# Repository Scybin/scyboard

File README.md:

# scyboard

## 📚 Table of Contents

- [⚠️ Disclaimer](#disclaimer)
- [⌨️ Welcome](#welcome)
- [⚙️ Features](#features)
- [📊 Project Status](#project-status)
- [📦 Parts List](#parts-list)
- [🛠️ Build Guide](#build-guide)
- [💾 Firmware](#firmware)
- [🙏 Thanks](#thanks)
- [📄 License](#license)

## ⚠️ Disclaimer

This project has reached the fully working prototype stage. All core features have been tested and function as intended. However, as with any DIY hardware project, you should carefully review all files before manufacturing or assembly. The author(s) cannot guarantee flawless operation in every environment or configuration.

The author(s) take no responsibility for any damage, issues, or legal trouble that might result from using this project (see the license). Be sure to follow local laws regarding radio frequencies and DIY electronics.

## ⌨️ Welcome

Scyboard is a custom, open-source mechanical keyboard designed for ergonomic comfort and wireless functionality. Inspired by the Sweep and Corne keyboards, scyboard builds on these layouts and design principles. Every aspect was created using open-source tools, making it easy to modify, build, and share.

## ⚙️ Features

- Compact layout optimized for ergonomics
- ZMK firmware support
- USB-C connectivity & battery charging
- Bluetooth compatible
- Customizable keymaps, layers, and macros
- Layout is declared using Ergogen
- KiCad traces auto-routed using Freerouting
- Open source

## 📊 Project Status

The prototype has been built successfully. All aspects of the keyboard and firmware behave as expected.

## 📦 Parts List

*I am not sponsored or affiliated with the vendors linked below. This is where I prefer to purchase my products.*

| Part                     | Quantity | Description                          | Purchase Link                                                                                                         | Datasheet                                                                                                                                                         |
|--------------------------|----------|--------------------------------------|-----------------------------------------------------------------------------------------------------------------------|-------------------------------------------------------------------------------------------------------------------------------------------------------------------|
| Microcontroller          |    2     | nice!nano v2.0                       | [Nice Keyboarrds nice!nano v2.0](https://typeractive.xyz/products/no-solder-spring-headers?variant=47196312502503)    | [Nordic nRF52840](https://nicekeyboards.com/nice-nano)                                                                                                            | 
| Pin Headers              |    4     | Controller socketing system          | [MAC8 spring-loaded pin headers](https://typeractive.xyz/products/no-solder-spring-headers?variant=47196312502503)    | [MAC8 spring-loaded pin headers specifications](https://www.mac8sdk.co.jp/uploads/entry_meta/file_value/1117/mac8_2018a_jp-xb2.pdf)                               |
| Reset Button             |    2     | Panasonic miniature momentary button | [Panasonic Reset Button](https://typeractive.xyz/products/reset-button)                                               | [EVQPUC02K](https://cdn.shopify.com/s/files/1/0618/5674/3655/files/PANASONIC-EVQPUC02K.pdf)                                                                       |
| Power Switch             |    2     | Alps miniature SPDT switch           | [ALPS Powr Switch](https://typeractive.xyz/products/power-switch)                                                     | [SSSS811101](https://cdn.shopify.com/s/files/1/0618/5674/3655/files/ALPS-SSSS811101.pdf)                                                                          |
| Battery Jack             |    2     | JST PH 2.0mm                         | [JST Battery Jack](https://typeractive.xyz/products/battery-jack)                                                     | [JST_PH_S2B-PH-K_1x02_P2.00mm_Horizontal](http://www.jst-mfg.com/product/pdf/eng/ePH.pdf)                                                                         |
| Battery                  |    2     | 3.7V LiPo 110mAh (w/ JST adapter)    | [Liter Bihuade Lithium Battery](https://typeractive.xyz/products/lithium-battery-110mah)                              | [301230](https://www.ufinebattery.com/images/upload/ufx0509-08-3-7v-75mah-lithium-ion-battery-product-datasheet.pdf)                                              |
| Diode                    |    44    | SMD Diode                            | [Semtech SMD Diodes](https://typeractive.xyz/products/smd-diodes)                                                     | [SOD-123](https://www.onsemi.com/download/data-sheet/pdf/mmsd301t1-d.pdf)      									                                                                 |
| Hotswap Socket           |    44    | Kailh Choc PCB Socket                | [Kailh Hotswap Sockets](https://typeractive.xyz/products/hotswap-sockets)                                             | [1350Connector](https://www.kailhswitch.com/Content/upload/pdf/202115927/CPG135001S30-data-sheet.pdf?rnd=943)                                                     |
| Choc V1/V2 Switch        |    44    | Kailh Choc                           | [Lowprokb Ambients Silent Choc Switches](https://lowprokb.ca/products/ambients-silent-choc-switches)                  |                                                                                                                                                                   |
| Choc Keycap              |    44    | 40 x 1u, 4 x 1.5u                    | [FK MBK Choc Keycaps](https://typeractive.xyz/products/mbk-keycaps)                                                   |                                                                                                                                                                   |
| Nut  (optional)          |    12    | Inserts for bottom case              | [uxcell Knurled Insert Nuts](https://www.amazon.com/dp/B07LBQFNQD?th=1)                                               |                                                                                                                                                                   |
| M2X3 Screw  (optional)   |    24    | Screws for bottom case               | [CO-RODE Screw Kit](https://www.amazon.com/gp/product/B01FTI8TM8/)                                                    |                                                                                                                                                                   |
| M2X4 Screw  (optional)   |    12    | Screws for bottom case               | [CO-RODE Screw Kit](https://www.amazon.com/gp/product/B01FTI8TM8/)                                                    |                                                                                                                                                                   |
| M2X6 Standoff (optional) |    10    | Standoffs for plate                  | [uxcell M2x6 Standoffs](https://a.co/d/fXHgMmH)                                                                       |                                                                                                                                                                   |
| Bottom Case (optional)   |    2     | 3D printed bottom case               | [Case STL Found Here](https://github.com/Scybin/scyboard/tree/master/3d)                                              |                                                                                                                                                                   |
| Plate (optional)         |    2     | 3D printed plate                     | [Plate STL Found Here](https://github.com/Scybin/scyboard/tree/master/3d)                                             |                                                                                                                                                                   | 
| Screw Spacers (optional) |    12    | 3D printed spacers                   | [Screw Spacer STL Found Here](https://github.com/Scybin/scyboard/tree/master/3d)                                      |                                                                                                                                                                   |

## 🛠️ Build Guide

For assembling the keyboard hardware, I recommend following the guide for the Corne keyboard, as the assembly process is similar. You can find the guide here: [corne-cherry v2 buildguide](https://github.com/foostan/crkbd/blob/main/docs/corne-cherry/v2/buildguide_en.md)

In addition, here are some specific notes for the scyboard:
- There will be slight differences in the assembly process due to the different components used, but the overall steps will be similar.
- Place the nice!nano V2 microcontroller face down (flat side facing up).
- Solder the MCU jumper pads on the *same* (top) side of the PCB where the MCU wis mounted.
- Solder the JST battery connector jumpper pads on the *opposite* (back) side of the PCB where the MCU is mounted.

You can use the 3D printed bottom case without a plate. This requires M2x4 screws on the top, M2X3 screws on the bottom, knurled insert nuts, and 3D printed screw spacers. To mount the PCB directly to the case, use the 3D printed screw spacers between the screw and PCB. 

If you want to add a plate to the build, you can replace the nuts and spacers by using M2x6 standoffs. I included files for a plate if you decide to go this route. You will need one insert nut and spacer for the hole next to the JST connector since the plate does not cover this area.

## 💾 Firmware

A ZMK module for this keyboard is available at:  
[zmk-keyboard-scyboard](https://github.com/Scybin/zmk-keyboard-scyboard)

To get started, add the module to your west.yaml file and follow the flashing instructions in the ZMK docs.

## 🙏 Thanks

- **[Ergogen](https://docs.ergogen.xyz/):** For keyboard PCB generation and configuration.
- **[Ceoloide](https://github.com/ceoloide/ergogen-footprints):** For providing footprints. An additional thanks for code inspiration.
- **[ZMK Firmware](https://zmk.dev/):** For providing the open-source keyboard architecture support.
- **[KiCad](https://www.kicad.org/):** For PCB viewing and editing.
- **[Freerouting](https://www.freerouting.app/):** For PCB auto-routing in KiCad.
- **[typeractive](https://typeractive.xyz/):** For design and parts inspiration.
- **[Sweep by David Philip Barr](https://github.com/davidphilipbarr/Sweep):** For key matrix and column stagger inspiration.
- **[Corne by foostan](https://github.com/foostan/crkbd):** For thumb cluster inspiration.
- **[FlatFootFox](https://flatfootfox.com/ergogen-introduction/):** For an Ergogen tutorial.
- **[nickcoutsos](https://nickcoutsos.github.io/keymap-editor/):** For the ZMK Keymap Editor browser app.
- **[joe-scotto](https://github.com/Scybin/scottokeebs/tree/dab518b84248842a73bc8f1feb84828ada38bbac/Extras/ScottoKicad):** For a 3d model library
- Open Source Community: For sharing knowledge, scripts, and inspiration.

## 📄 License

This project is licensed under the MIT License. See the [LICENSE](LICENSE) file for details.

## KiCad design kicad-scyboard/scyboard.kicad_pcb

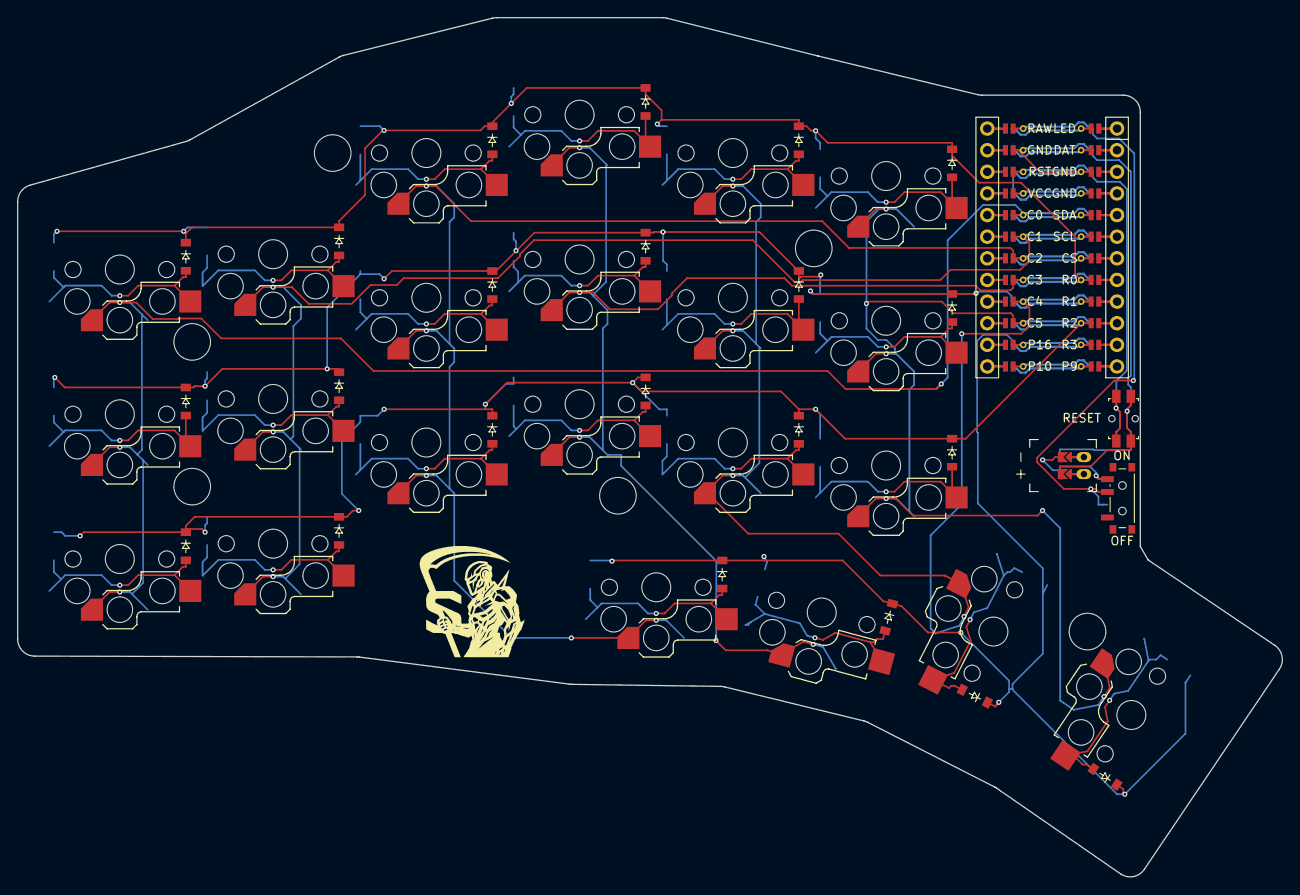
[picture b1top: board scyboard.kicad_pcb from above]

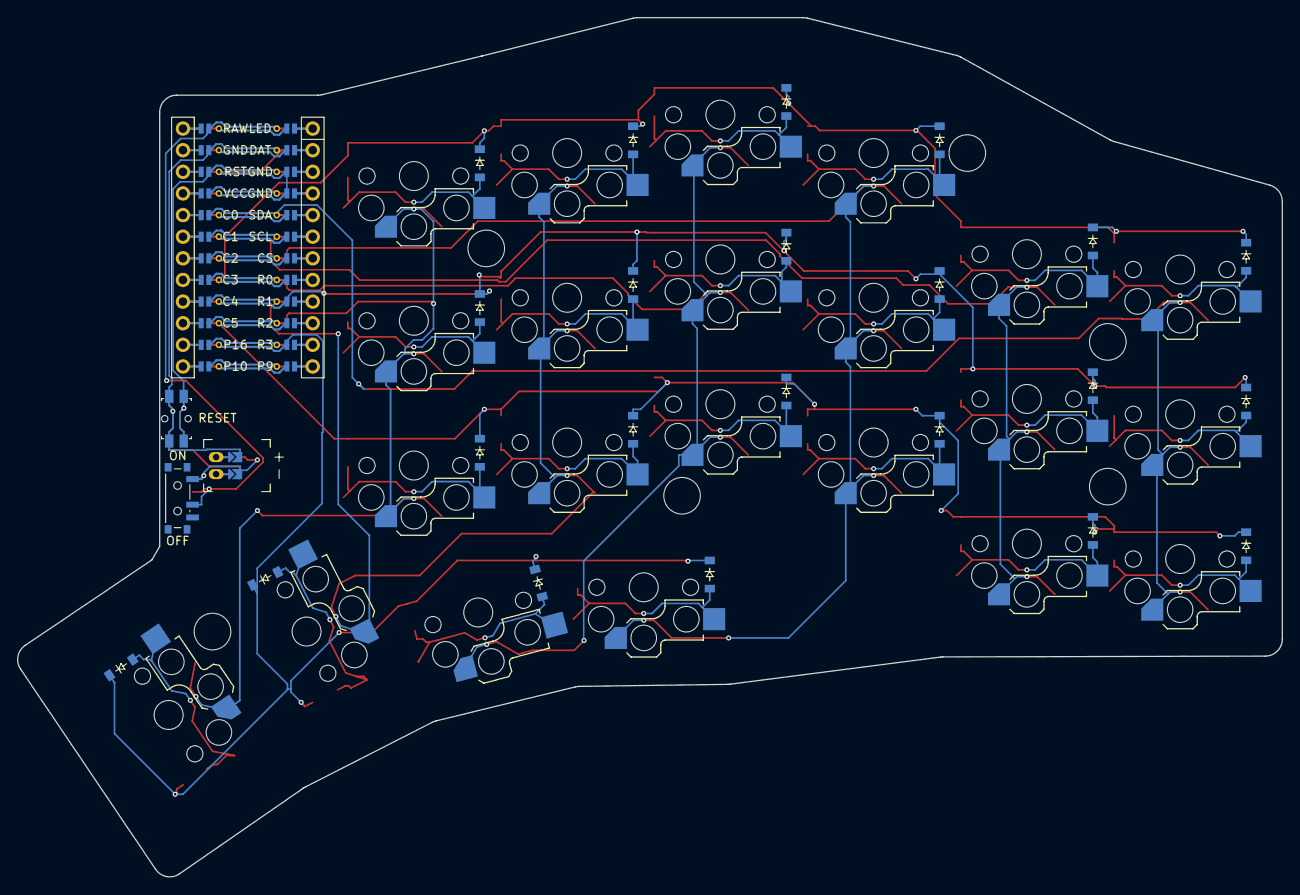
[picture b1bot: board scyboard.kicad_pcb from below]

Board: 2 copper layers, 148.5 x 100.9 mm, 76 parts (44 on the bottom side), 38 nets.

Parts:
D1, D2, D3, D4, D5, D6, D7, D8, D9, D10, D11, D12, D13, D14, D15, D16, D17, D18, D19, D20, D21, D22, D23, D24, D25, D26, D27, D28, D29, D30, D31, D32, D33, D34, D35, D36, D37, D38, D39, D40, D41, D42, D43, D44: diode_tht_sod123
JST1: battery_connector_jst_ph_2
MCU1: mcu_nice_nano
MH1, MH2, MH3, MH4, MH5, MH6: mounting_hole_npth
PWR1: power_switch_smd_side
RST1: reset_switch_smd_side
S1, S2, S3, S4, S5, S6, S7, S8, S9, S10, S11, S12, S13, S14, S15, S16, S17, S18, S19, S20, S21, S22: switch_choc_v1_v2

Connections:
BAT_P: JST1.1, PWR1.1, PWR1.3
C0: MCU1.120, S1.1, S2.1, S3.1
C1: MCU1.119, S4.1, S5.1, S6.1
C2: MCU1.118, S7.1, S8.1, S9.1, S19.1
C3: MCU1.117, S10.1, S11.1, S12.1, S20.1
C4: MCU1.116, S13.1, S14.1, S15.1, S21.1
C5: MCU1.115, S16.1, S17.1, S18.1, S22.1
GND: JST1.2, MCU1.103, MCU1.104, MCU1.123, RST1.1, RST1.3
JST1_1: JST1.11, JST1.21, JST1.31
JST1_2: JST1.12, JST1.22, JST1.32
R0: D3.1, D6.1, D9.1, D12.1, D15.1, D18.1, D25.1, D28.1, D31.1, D34.1, D37.1, D40.1, MCU1.108
R1: D2.1, D5.1, D8.1, D11.1, D14.1, D17.1, D24.1, D27.1, D30.1, D33.1, D36.1, D39.1, MCU1.109
R2: D1.1, D4.1, D7.1, D10.1, D13.1, D16.1, D23.1, D26.1, D29.1, D32.1, D35.1, D38.1, MCU1.110
R3: D19.1, D20.1, D21.1, D22.1, D41.1, D42.1, D43.1, D44.1, MCU1.111
RAW: MCU1.124, PWR1.2
RST: MCU1.122, RST1.2, RST1.4
index_bottom_B: D13.2, D35.2, S13.2
index_home_B: D14.2, D36.2, S14.2
index_top_B: D15.2, D37.2, S15.2
inner_bottom_B: D16.2, D38.2, S16.2
inner_home_B: D17.2, D39.2, S17.2
inner_top_B: D18.2, D40.2, S18.2
layer_cluster_B: D20.2, D42.2, S20.2
middle_bottom_B: D10.2, D32.2, S10.2
middle_home_B: D11.2, D33.2, S11.2
middle_top_B: D12.2, D34.2, S12.2
outer_bottom_B: D1.2, D23.2, S1.2
outer_home_B: D2.2, D24.2, S2.2
outer_top_B: D3.2, D25.2, S3.2
pinky_bottom_B: D4.2, D26.2, S4.2
pinky_home_B: D5.2, D27.2, S5.2
pinky_top_B: D6.2, D28.2, S6.2
reach_cluster_B: D22.2, D44.2, S22.2
ring_bottom_B: D7.2, D29.2, S7.2
ring_home_B: D8.2, D30.2, S8.2
ring_top_B: D9.2, D31.2, S9.2
space_cluster_B: D21.2, D43.2, S21.2
tuck_cluster_B: D19.2, D41.2, S19.2

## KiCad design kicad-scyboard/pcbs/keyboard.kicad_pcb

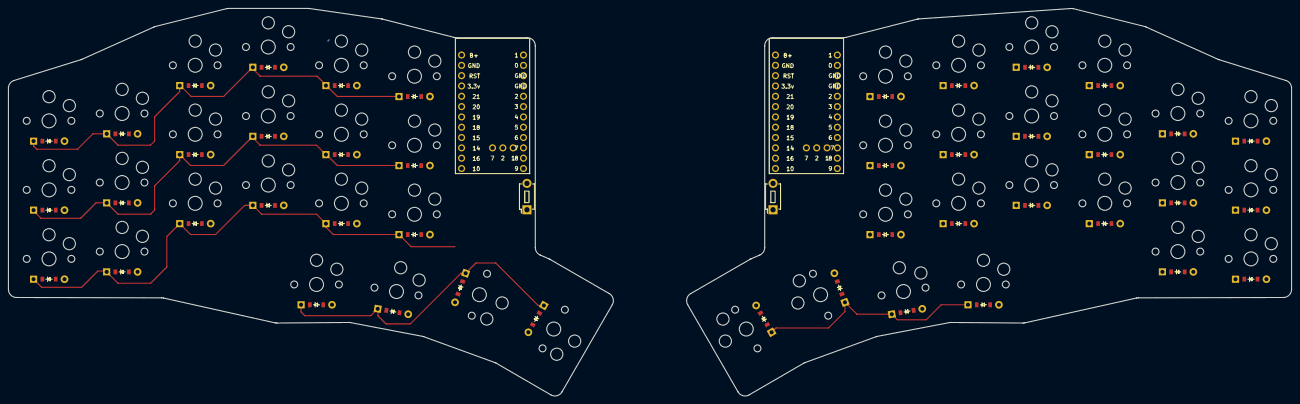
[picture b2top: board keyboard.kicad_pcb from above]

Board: 2 copper layers, 316.0 x 95.4 mm, 90 parts (0 on the bottom side), 46 nets.

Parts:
D1, D2, D3, D4, D5, D6, D7, D8, D9, D10, D11, D12, D13, D14, D15, D16, D17, D18, D19, D20, D21, D22, D23, D24, D25, D26, D27, D28, D29, D30, D31, D32, D33, D34, D35, D36, D37, D38, D39, D40, D41, D42, D43, D44: ComboDiode
S1, S2, S3, S4, S5, S6, S7, S8, S9, S10, S11, S12, S13, S14, S15, S16, S17, S18, S19, S20, S21, S22, S23, S24, S25, S26, S27, S28, S29, S30, S31, S32, S33, S34, S35, S36, S37, S38, S39, S40, S41, S42, S43, S44: PG1350
U1, U1#2: Nice_Nano_V2_Flipped

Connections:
P0: S13.1, S14.1, S15.1, S35.1, S36.1, S37.1
P1: D1.1, D4.1, D7.1, D10.1, D13.1, D16.1, D23.1, D26.1, D29.1, D32.1, D35.1, D38.1
index_bottom: D13.2, S13.2
index_home: D14.2, S14.2
index_top: D15.2, S15.2
inner_bottom: D16.2, S16.2
inner_home: D17.2, S17.2
inner_top: D18.2, S18.2
layer_cluster: D20.2, S20.2
middle_bottom: D10.2, S10.2
middle_home: D11.2, S11.2
middle_top: D12.2, S12.2
mirror_index_bottom: D35.2, S35.2
mirror_index_home: D36.2, S36.2
mirror_index_top: D37.2, S37.2
mirror_inner_bottom: D38.2, S38.2
mirror_inner_home: D39.2, S39.2
mirror_inner_top: D40.2, S40.2
mirror_layer_cluster: D42.2, S42.2
mirror_middle_bottom: D32.2, S32.2
mirror_middle_home: D33.2, S33.2
mirror_middle_top: D34.2, S34.2
mirror_outer_bottom: D23.2, S23.2
mirror_outer_home: D24.2, S24.2
mirror_outer_top: D25.2, S25.2
mirror_pinky_bottom: D26.2, S26.2
mirror_pinky_home: D27.2, S27.2
mirror_pinky_top: D28.2, S28.2
mirror_reach_cluster: D44.2, S44.2
mirror_ring_bottom: D29.2, S29.2
mirror_ring_home: D30.2, S30.2
mirror_ring_top: D31.2, S31.2
mirror_space_cluster: D43.2, S43.2
mirror_tuck_cluster: D41.2, S41.2
outer_bottom: D1.2, S1.2
outer_home: D2.2, S2.2
outer_top: D3.2, S3.2
pinky_bottom: D4.2, S4.2
pinky_home: D5.2, S5.2
pinky_top: D6.2, S6.2
reach_cluster: D22.2, S22.2
ring_bottom: D7.2, S7.2
ring_home: D8.2, S8.2
ring_top: D9.2, S9.2
space_cluster: D21.2, S21.2
tuck_cluster: D19.2, S19.2

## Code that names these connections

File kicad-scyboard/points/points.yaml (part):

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        autobind: 10
        skip: false
        asym: both
        colrow: pinky_bottom
        name: matrix_pinky_bottom
        zone: *ref_0
        col: *ref_2
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        autobind: 10
        skip: false
        asym: both
        colrow: pinky_home
        name: matrix_pinky_home
        zone: *ref_0
        col: *ref_2
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        autobind: 10
        skip: false
        asym: both
        colrow: pinky_top
        name: matrix_pinky_top
        zone: *ref_0
        col: *ref_2
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        autobind: 10
        skip: false
        asym: both
        colrow: mirror_pinky_bottom
        name: mirror_matrix_pinky_bottom
        zone:
            key:
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        autobind: 10
        skip: false
        asym: both
        colrow: mirror_pinky_home
        name: mirror_matrix_pinky_home
        zone:
            key:
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        autobind: 10
        skip: false
        asym: both
        colrow: mirror_pinky_top
        name: mirror_matrix_pinky_top
        zone:
            key:
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
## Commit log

2025-05-29 Add .gitattributes, .gitignore, README.md, and LICENSE.txt.
2025-05-29 Add project files.
2025-05-29 Compile
2025-05-30 Add matrix image
2025-05-30 Add nicenano pinout and schematics
2025-05-30 Update matrix
2025-05-30 Move pictures to folder
2025-05-31 Update kicad
2025-06-02 Add ceoloide footprints
2025-06-02 Add ceoloide footprint
2025-06-02 Update parts list
2025-06-05 Reverse mount MCU
2025-06-05 Generate PCB
2025-06-08 Add KiCad pcb
2025-06-08 Add Gerbers
2025-06-10 Update PCB
2025-06-10 Remove case and drill holes from config
2025-06-10 Update README.md
    Add bottom case, nuts, and screws to parts list.
2025-06-10 Update README.md
    Reformat readme
2025-06-10 Update README.md
    Correct purchase link for m2 screws
2025-06-11 Generate gerbers
2025-06-11 Add top and bottom JLCPCB Prototype photos
2025-06-11 Exclude VS .sln file
2025-06-11 Remove .sln
2025-06-15 Update README.md
    Add ZMK Firmware & special thanks to ZMK Keymap Editor
2025-06-20 Add picutre of the scyboard final build
2025-06-21 Add build guide and remove TODO list
2025-06-21 Fix formatting in build guide
2025-06-22 Fix readme anchors
2025-06-22 Mill-Max General Technical Specifications datasheet
2025-06-22 Add Mill-Max General Technical Specifications datasheet
2025-06-27 Clarify jumper pad solder positions in Build Guide
    Update README.md
2025-06-27 Clarify MCU placement in build guide
2025-06-27 Minor formatting changes
2025-06-28 Add plate files
2025-06-28 Upload build photos
2025-06-28 Update scyboard photo
2025-06-28 Add case assembly to the build guide
2025-06-28 Add assembled case image
2025-06-28 Add case photos
2025-06-28 Formatting changes
2025-06-28 Update project status
2025-06-28 Update disclaimer
2025-06-28 Update plate 3D files
2025-06-28 Add scyboard build photos
2025-06-28 Add scyboard plated photo
2025-06-28 Add screw spacer image
2025-06-28 Update parts list for case materials
2025-06-28 Update parts descriptions
2025-06-28 Update screw spacer 3D file
2025-06-28 Add links to 3D print STL files
2025-06-28 Update build guide
2025-07-12 Update ZMK module instructions
2025-07-12 Update License
2025-07-12 Clean up formatting
2025-12-10 Update README.md
    Include disclaimer regarding firmware revisions that are necessary to support the Zephyr 4.1 update.
2025-12-11 Update README.md
    Remove IMPORTANT note from readme regarding Zephyr 4.1 Update
2025-12-28 Add credit for 3D model library by joe-scotto
2025-12-28 Update quantity of Machine Sockets and Pins to 4
    Purchase 2x units, which = 4x parts
2025-12-28 Change 'Machine Sockets and Pins' to 'Pin Headers'
    Updated component names and links in the parts list.
